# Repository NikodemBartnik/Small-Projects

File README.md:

# Small Projects
Here you can find some of my smaller projects. Most of them are Arduino based, there are also schematics and PCB design files. Feel free to fork and make it even better! Don't forget to share with others and with me, I would love to see how you adapt those small projects into something bigger :)

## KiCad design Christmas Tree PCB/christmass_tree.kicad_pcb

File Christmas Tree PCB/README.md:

# Christmas-Tree-PCB
Last Christmas I made 3D printed cookie cutters and this Christmas I wanted to make a cool electronics project. I designed a Christmas tree PCB in kicad and then ordered it online at jlcpcb.com. Few LEDs, 2 10 Ohm resistors, battery box and you have a great Christmas ornament or gift :)

https://www.youtube.com/watch?v=JdUFrBdkSZM

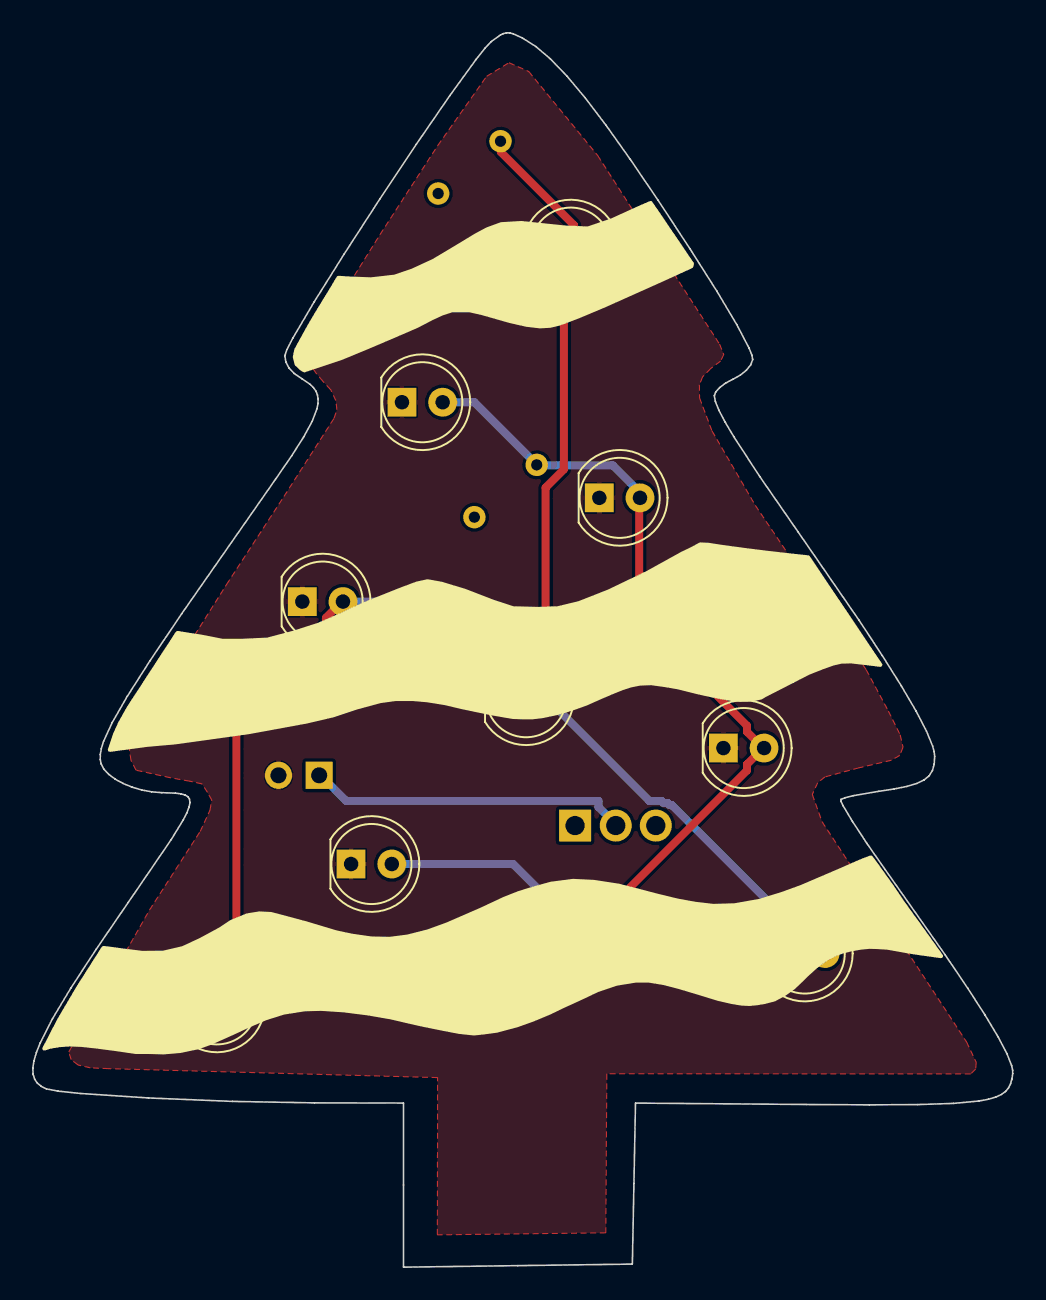
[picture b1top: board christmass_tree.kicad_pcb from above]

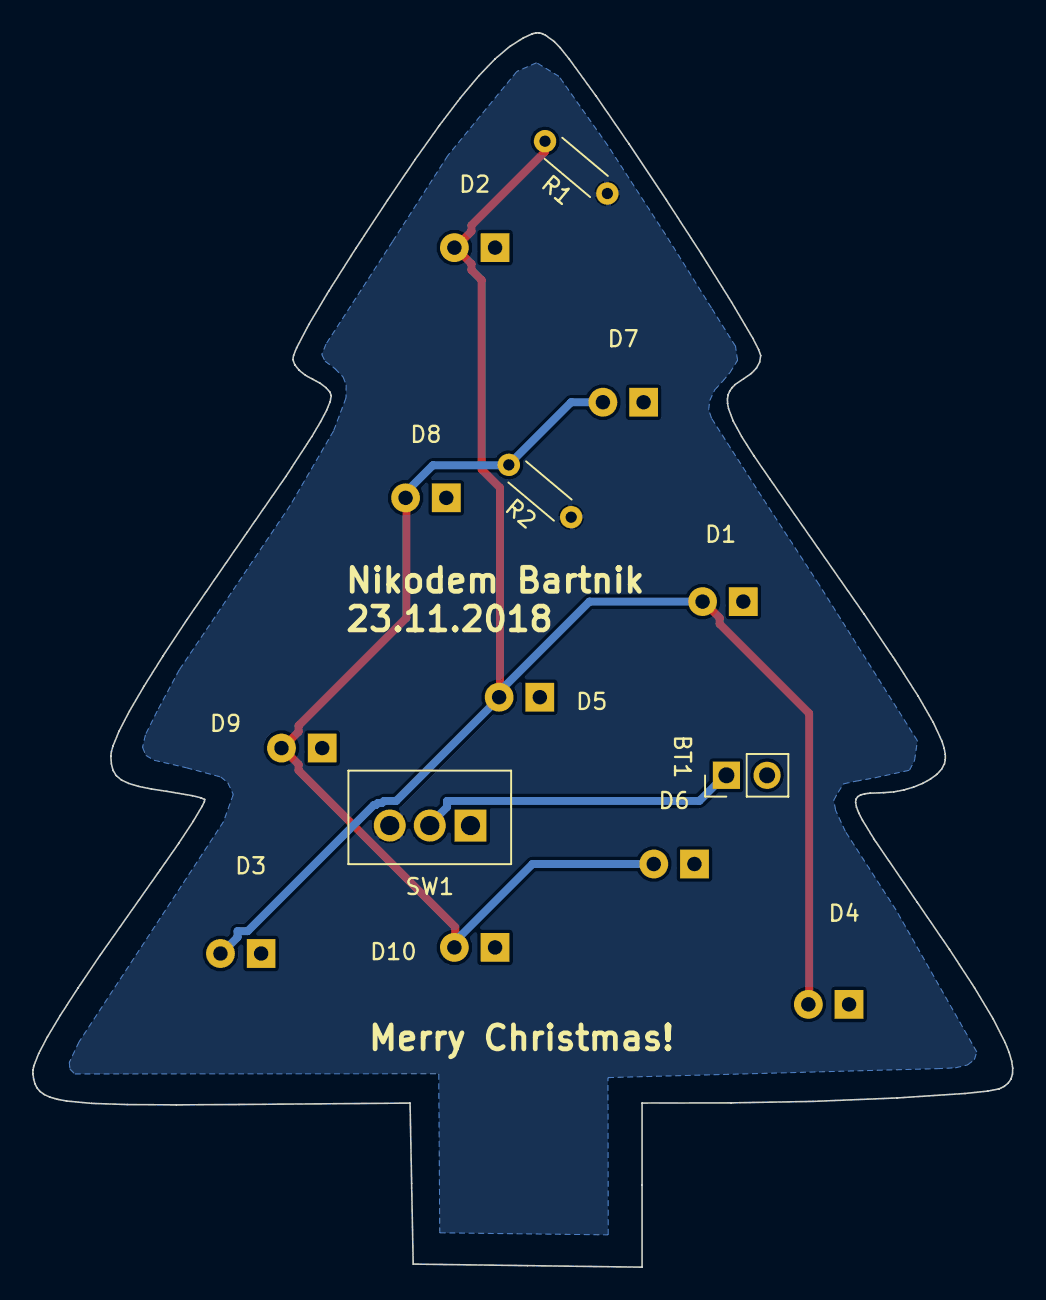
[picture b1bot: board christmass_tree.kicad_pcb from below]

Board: 2 copper layers, 61.2 x 77.1 mm, 14 parts (4 on the bottom side), 5 nets.

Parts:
BT1: Battery; Pin_Header_Straight_1x02_Pitch2.54mm
D1, D2, D3, D4, D5, D6, D7, D8, D9, D10: LED; LED_D5.0mm
R1, R2: 10; R_Axial_DIN0204_L3.6mm_D1.6mm_P5.08mm_Horizontal
SW1: SW_DPDT_x2; Wafer_Vertical10x5.8x7RM2.5-3

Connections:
GND: BT1.2, D1.1, D2.1, D3.1, D4.1, D5.1, D6.1, D7.1, D8.1, D9.1, D10.1
unnamed: BT1.1, SW1.2
unnamed: D1.2, D2.2, D3.2, D4.2, D5.2, R1.2
unnamed: D6.2, D7.2, D8.2, D9.2, D10.2, R2.2
VCC: R1.1, R2.1, SW1.3

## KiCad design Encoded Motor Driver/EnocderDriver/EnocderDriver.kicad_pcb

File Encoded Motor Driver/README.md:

# EncoderMotorDriver

Simple project of Arduino based encoder driver that communicates over I2C to make it easy to use motors with encoders in any Arduino based project. You can find here a source code and design files for the PCB, for more info check out my YouTube video:
<br/>

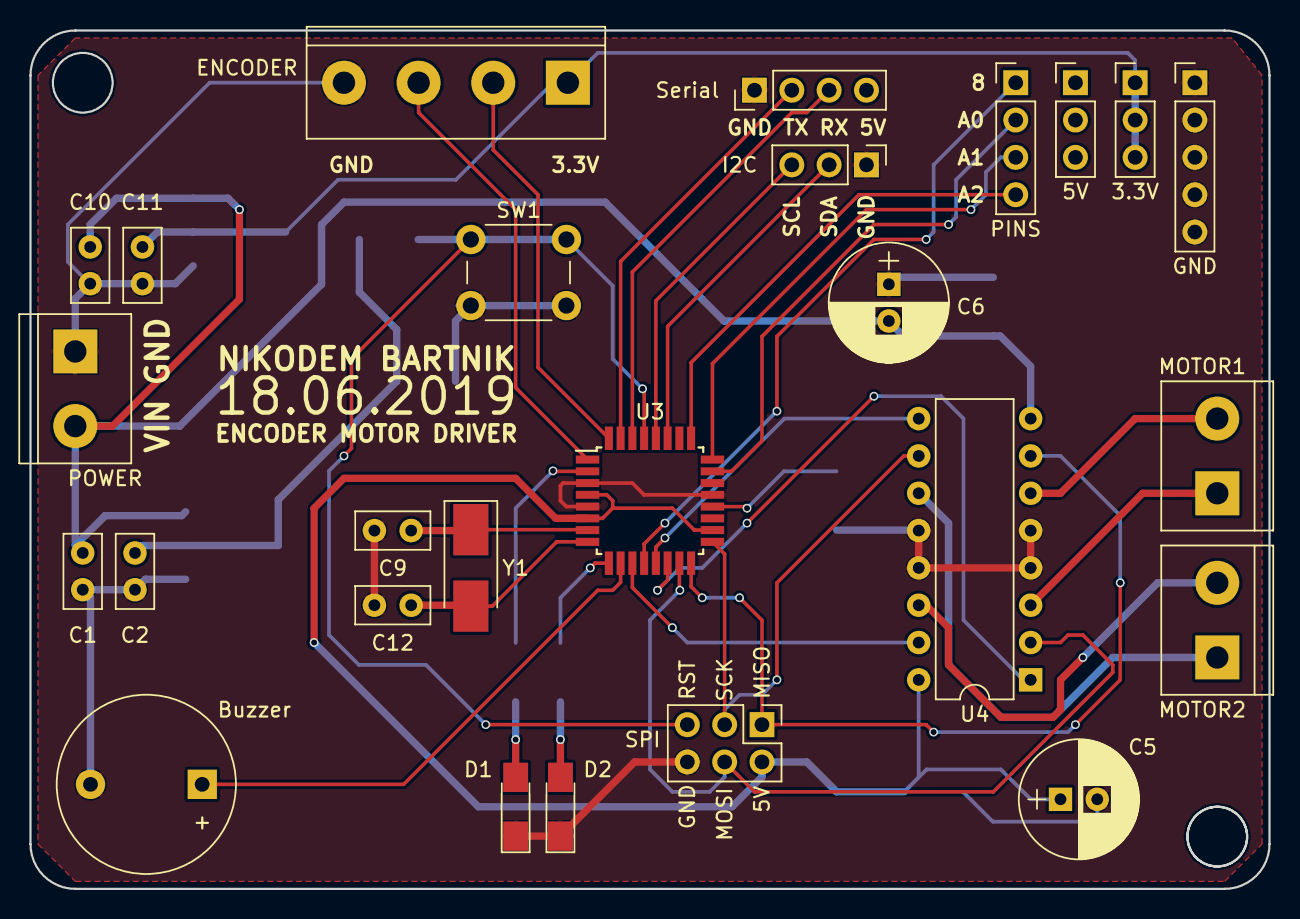
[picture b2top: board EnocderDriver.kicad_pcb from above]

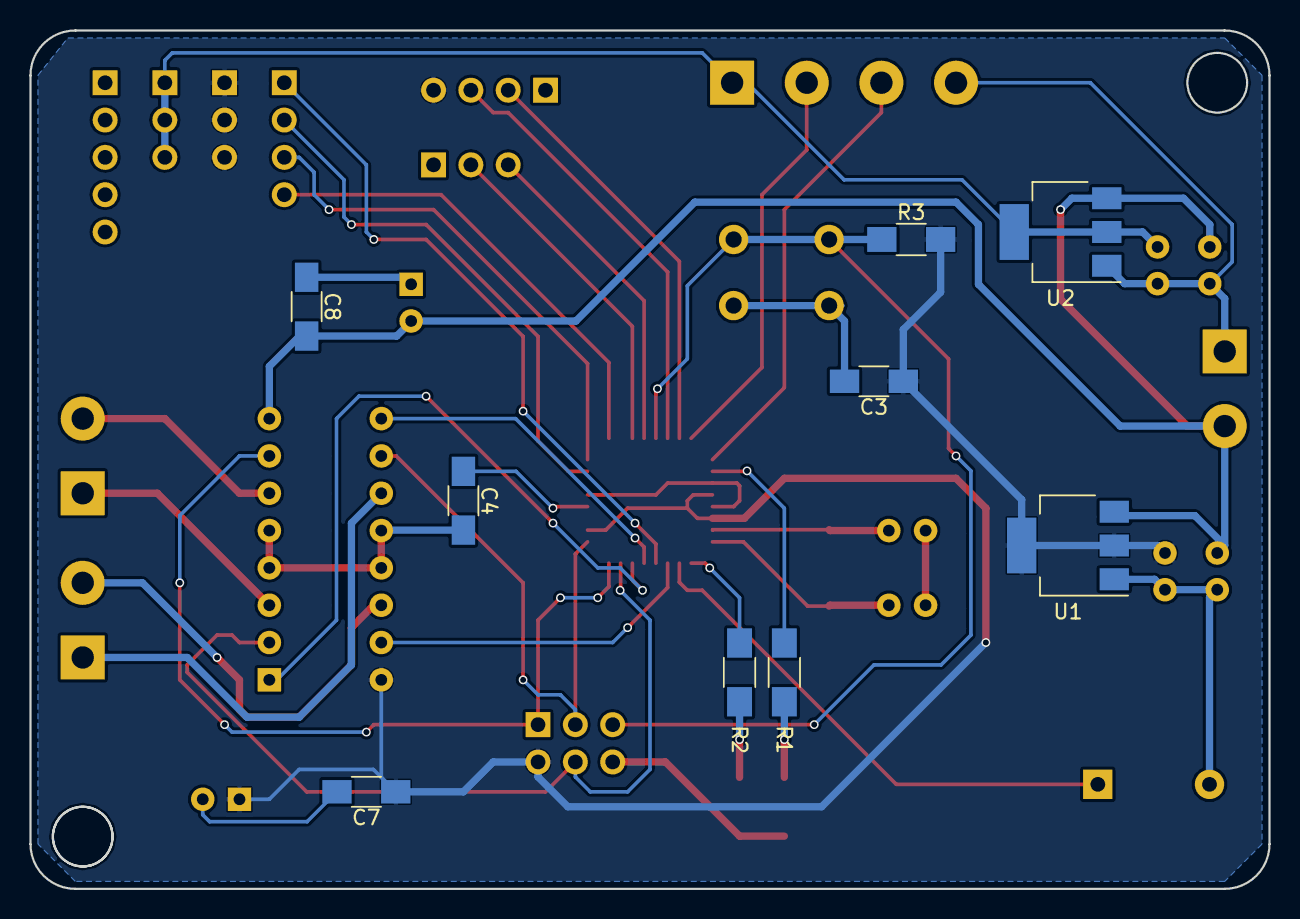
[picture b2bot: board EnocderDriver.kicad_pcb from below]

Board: 2 copper layers, 84.3 x 58.4 mm, 35 parts (9 on the bottom side), 33 nets.

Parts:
BZ1: Buzzer; Buzzer_12x9.5RM7.6
C1, C2, C10, C11: 10U; C_Disc_D5.0mm_W2.5mm_P2.50mm
C3, C4: C; C_1206_HandSoldering
C5: 10u; CP_Radial_D8.0mm_P2.50mm
C6: 22u; CP_Radial_D8.0mm_P2.50mm
C7, C8: 100n; C_1206_HandSoldering
C9, C12: C; C_Disc_D5.0mm_W2.5mm_P2.50mm
D1, D2: LED; LED_1206_HandSoldering
J1: POWER; TerminalBlock_bornier-2_P5.08mm
J2: PINS; Pin_Header_Straight_1x04_Pitch2.54mm
J3: 3.3V; Pin_Header_Straight_1x03_Pitch2.54mm
J4: 5V; Pin_Header_Straight_1x03_Pitch2.54mm
J5: GND; Pin_Header_Straight_1x05_Pitch2.54mm
J6: MOTOR1; TerminalBlock_bornier-2_P5.08mm
J7: MOTOR2; TerminalBlock_bornier-2_P5.08mm
J8: ENCODER; TerminalBlock_bornier-4_P5.08mm
J9: SPI; Pin_Header_Straight_2x03_Pitch2.54mm
J10: Serial; Socket_Strip_Straight_1x04_Pitch2.54mm
J11: I2C; Socket_Strip_Straight_1x03_Pitch2.54mm
R1, R2, R3: R; R_1206_HandSoldering
SW1: SW_Push; SW_PUSH_6mm
U1: LM1117-5.0; SOT-223-3_TabPin2
U2: LM1117-3.3; SOT-223-3_TabPin2
U3: ATMEGA8-16AU; TQFP-32_7x7mm_Pitch0.8mm
U4: L293D; DIP-16_W7.62mm
Y1: Crystal; Crystal_SMD_5032-2pin_5.0x3.2mm_HandSoldering

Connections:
+3V3: C11.1, J3.1, J3.2, J3.3, J8.1, U2.2
+5V: C2.1, C3.1, C5.1, C7.1, J4.1, J4.2, J4.3, J9.2, J10.4, R3.2, U1.2, U3.4, U3.6, U3.18, U4.16
+12V: C1.1, C6.2, C8.2, C10.1, J1.2, U1.3, U2.3, U4.8
BUZZER: BZ1.1, U3.10
GND: BZ1.2, C1.2, C2.2, C3.2, C4.2, C5.2, C6.1, C7.2, C8.1, C9.2, C10.2, C11.2, C12.2, D1.1, D2.1, J1.1, J5.1, J5.2, J5.3, J5.4, J5.5, J8.4, J9.6, J10.1, J11.1, SW1.2, U1.1, U2.1, U3.3, U3.5, U3.21, U4.4, U4.5, U4.12, U4.13
LED1: R1.2, U3.2
LED2: R2.2, U3.9
MDIR2: U3.11, U4.15
MISO: J9.1, U3.16, U4.7
MOSI: J9.4, U3.15, U4.2
unnamed: C4.1, U3.20
unnamed: C9.1, U3.7, Y1.1
unnamed: C12.1, U3.8, Y1.2
unnamed: D1.2, R1.1
unnamed: D2.2, R2.1
unnamed: J6.1, U4.3
unnamed: J6.2, U4.6
unnamed: J7.1, U4.11
unnamed: J7.2, U4.14
unnamed: J8.2, U3.32
unnamed: J8.3, U3.1
PIN1: J2.1, U3.12
PIN2: J2.2, U3.23
PIN3: J2.3, U3.24
PIN4: J2.4, U3.25
PWMA: U3.14, U4.1
PWMB: U3.13, U4.9
RESET: J9.5, R3.1, SW1.1, U3.29
RX: J10.3, U3.30
SCK: J9.3, U3.17, U4.10
SCL: J11.3, U3.28
SDA: J11.2, U3.27
TX: J10.2, U3.31

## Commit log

2021-01-14 Moved Encoded Motor driver from separete repo
2021-01-14 Moved sprint race timer repo
2021-01-14 Moved christmass tree PCB repo
2021-01-14 Moved RC Robot repo
2021-01-14 Moved Watering System repo
2021-03-03 Added Soldering Challenge files
